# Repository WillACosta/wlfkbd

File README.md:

## The Wolf Split Keyboard

> 3×6 (+2 outer-pinky) Split Keyboard · 3 Thumb Keys · All 1U · MX Compatible

The **WᛝLF Keyboard**, or **wlfkbd**, is a 40-key keyboard featuring only 2 outer-pinky keys to improve ergonomics, white backlight and RGB status LEDs.

> <br>
> Thanks to [JLCCNC](https://jlccnc.com/about-us) for sponsoring the production of the aluminum case. New customers can receive a total of $70 in coupons, so if you haven't used them yet, please check them out.

### Features

- Wireless BLE XIAO nRF52840.
- Ultra-low-profile build (8mm case and 11mm total).
- Lightweight (only 300 g for both halves).
- MX-Spacing.
- Compatible with Gateron KS33/3.0 Low-Profile switches.
- Long battery life (700mAh each half).
- Minimalist design.
- White backlight.
- RGB Status LEDs.

## Firmware & Keymap

The firmware for The Wolf is powered by [ZMK](https://zmk.dev/) and is maintained in its dedicated repository: **[zmk-config-wlf](https://github.com/WillACosta/zmk-config-wlf)**

This repository links the firmware as a Git submodule under [`firmware/`](https://github.com/WillACosta/zmk-config-wlf). To clone both the hardware designs and firmware together:

```bash
git clone --recurse-submodules https://github.com/WillACosta/wlfkbd.git
```

## Documentation

- [Gallery and Keymap](https://willacosta.github.io/wlfkbd/)
- [Build Guide](./docs/build_guide)
- [Measures and Materials tables](./docs/build_guide/tables.md)
- [Flashing Instructions](https://github.com/WillACosta/zmk-config-wlf/blob/main/README.md#flashing-instructions)

## Layout Overview

| Zone      | Columns                | Rows                  | Keys/half | Notes                                       |
| --------- | ---------------------- | --------------------- | --------- | ------------------------------------------- |
| Matrix    | 6 (outer → inner)      | 3 (bottom, home, top) | 17        | Outer column skips bottom row (2 keys only) |
| Thumb     | 3 (inner, home, outer) | 1                     | 3         | Splayed arc, anchored below index           |
| **Total** |                        |                       | **20**    | **40 keys full board**                      |

### Column Stagger Profile

```
         outer  pinky  ring   middle  index  inner
stagger:   —    +u/2   +u/4   +u/4   −u/4   −u/4
mm:        0    +9.525 +4.763 +4.763 −4.763 −4.763
```

**Thumb Cluster Geometry**

| Key         | Splay | Spread          | Stagger | Effective rotation |
| ----------- | ----- | --------------- | ------- | ------------------ |
| thumb_inner | 0°    | u (19.05mm)     | 0mm     | 0°                 |
| thumb_home  | −15°  | u+2.5 (21.55mm) | −2.7mm  | −15°               |
| thumb_outer | −14°  | u+2.5 (21.55mm) | −2.5mm  | −29°               |

The thumb cluster anchors at `matrix_index_bottom` with a `[-0.1u, -1.30u]` offset, placing it slightly left and well below the index column — a natural resting position for the thumb.

> See the Ergogen [config file here](./keyboard/ergogen/config.yml) (used only for the layout diagram)

## Motivations

After stepping into the rabbit hole of "Custom Split Keyboards", I found myself fascinated by this new world of different keyboard layouts, techniques, and a lot of fun!

I have used and own some beloved models created by incredible people, including:

- [Corne](https://github.com/foostan/crkbd)
- [Klor](https://github.com/GEIGEIGEIST/KLOR)
- [Delta/Omega](https://github.com/unspecworks/delta-omega)
- [Lily58](https://github.com/kata0510/Lily58)

The Corne is my favorite keyboard out there (you may notice some similarities between the wlfkbd and crkbd).

Still, I was missing something—that little thing that would improve my experience with the keyboard. Then I started testing different layouts on paper and came up with the layout shown earlier. I even used [Ergo Pad](https://pashutk.com/ergopad/) to find the most comfortable way of typing for my long fingers.

### Features

I'm very fond of good, minimal design, so I've taken inspiration from Apple products, especially the [Magic Keyboard](https://www.ifixit.com/Teardown/Magic+Keyboard+Teardown/50995) and [Magic Trackpad](https://www.ifixit.com/Teardown/Magic+Trackpad+2+Teardown/51032).

I really enjoy the white backlight of the built-in Mac keyboard, so I wanted to implement this in the first revision. Even though I only use the backlight occasionally, it's a nice-to-have for me.

The major feature I present here is the status LED on top of the outer-pinky column. It's something that I really wanted to have in previous keyboards but hadn't.

> For more pictures head to the [gallery](https://willacosta.github.io/wlfkbd/)

## Why "The WᛝLF"?

I really enjoy the symbolism of Wolves, it reminds me of the raw aspect of being human and a strong connection with nature and solitude. Regarding the Norse rune, the "Inguz", it represents "transitions", "new beginnings", "a force of will", etc. I have it tattooed on my right arm, so it's also a personal reference.

## PCB Design

The PCB was built to be ordered already assembled. This means that all components are SMD, so while you may be able to solder them by hand, it requires solid soldering experience.

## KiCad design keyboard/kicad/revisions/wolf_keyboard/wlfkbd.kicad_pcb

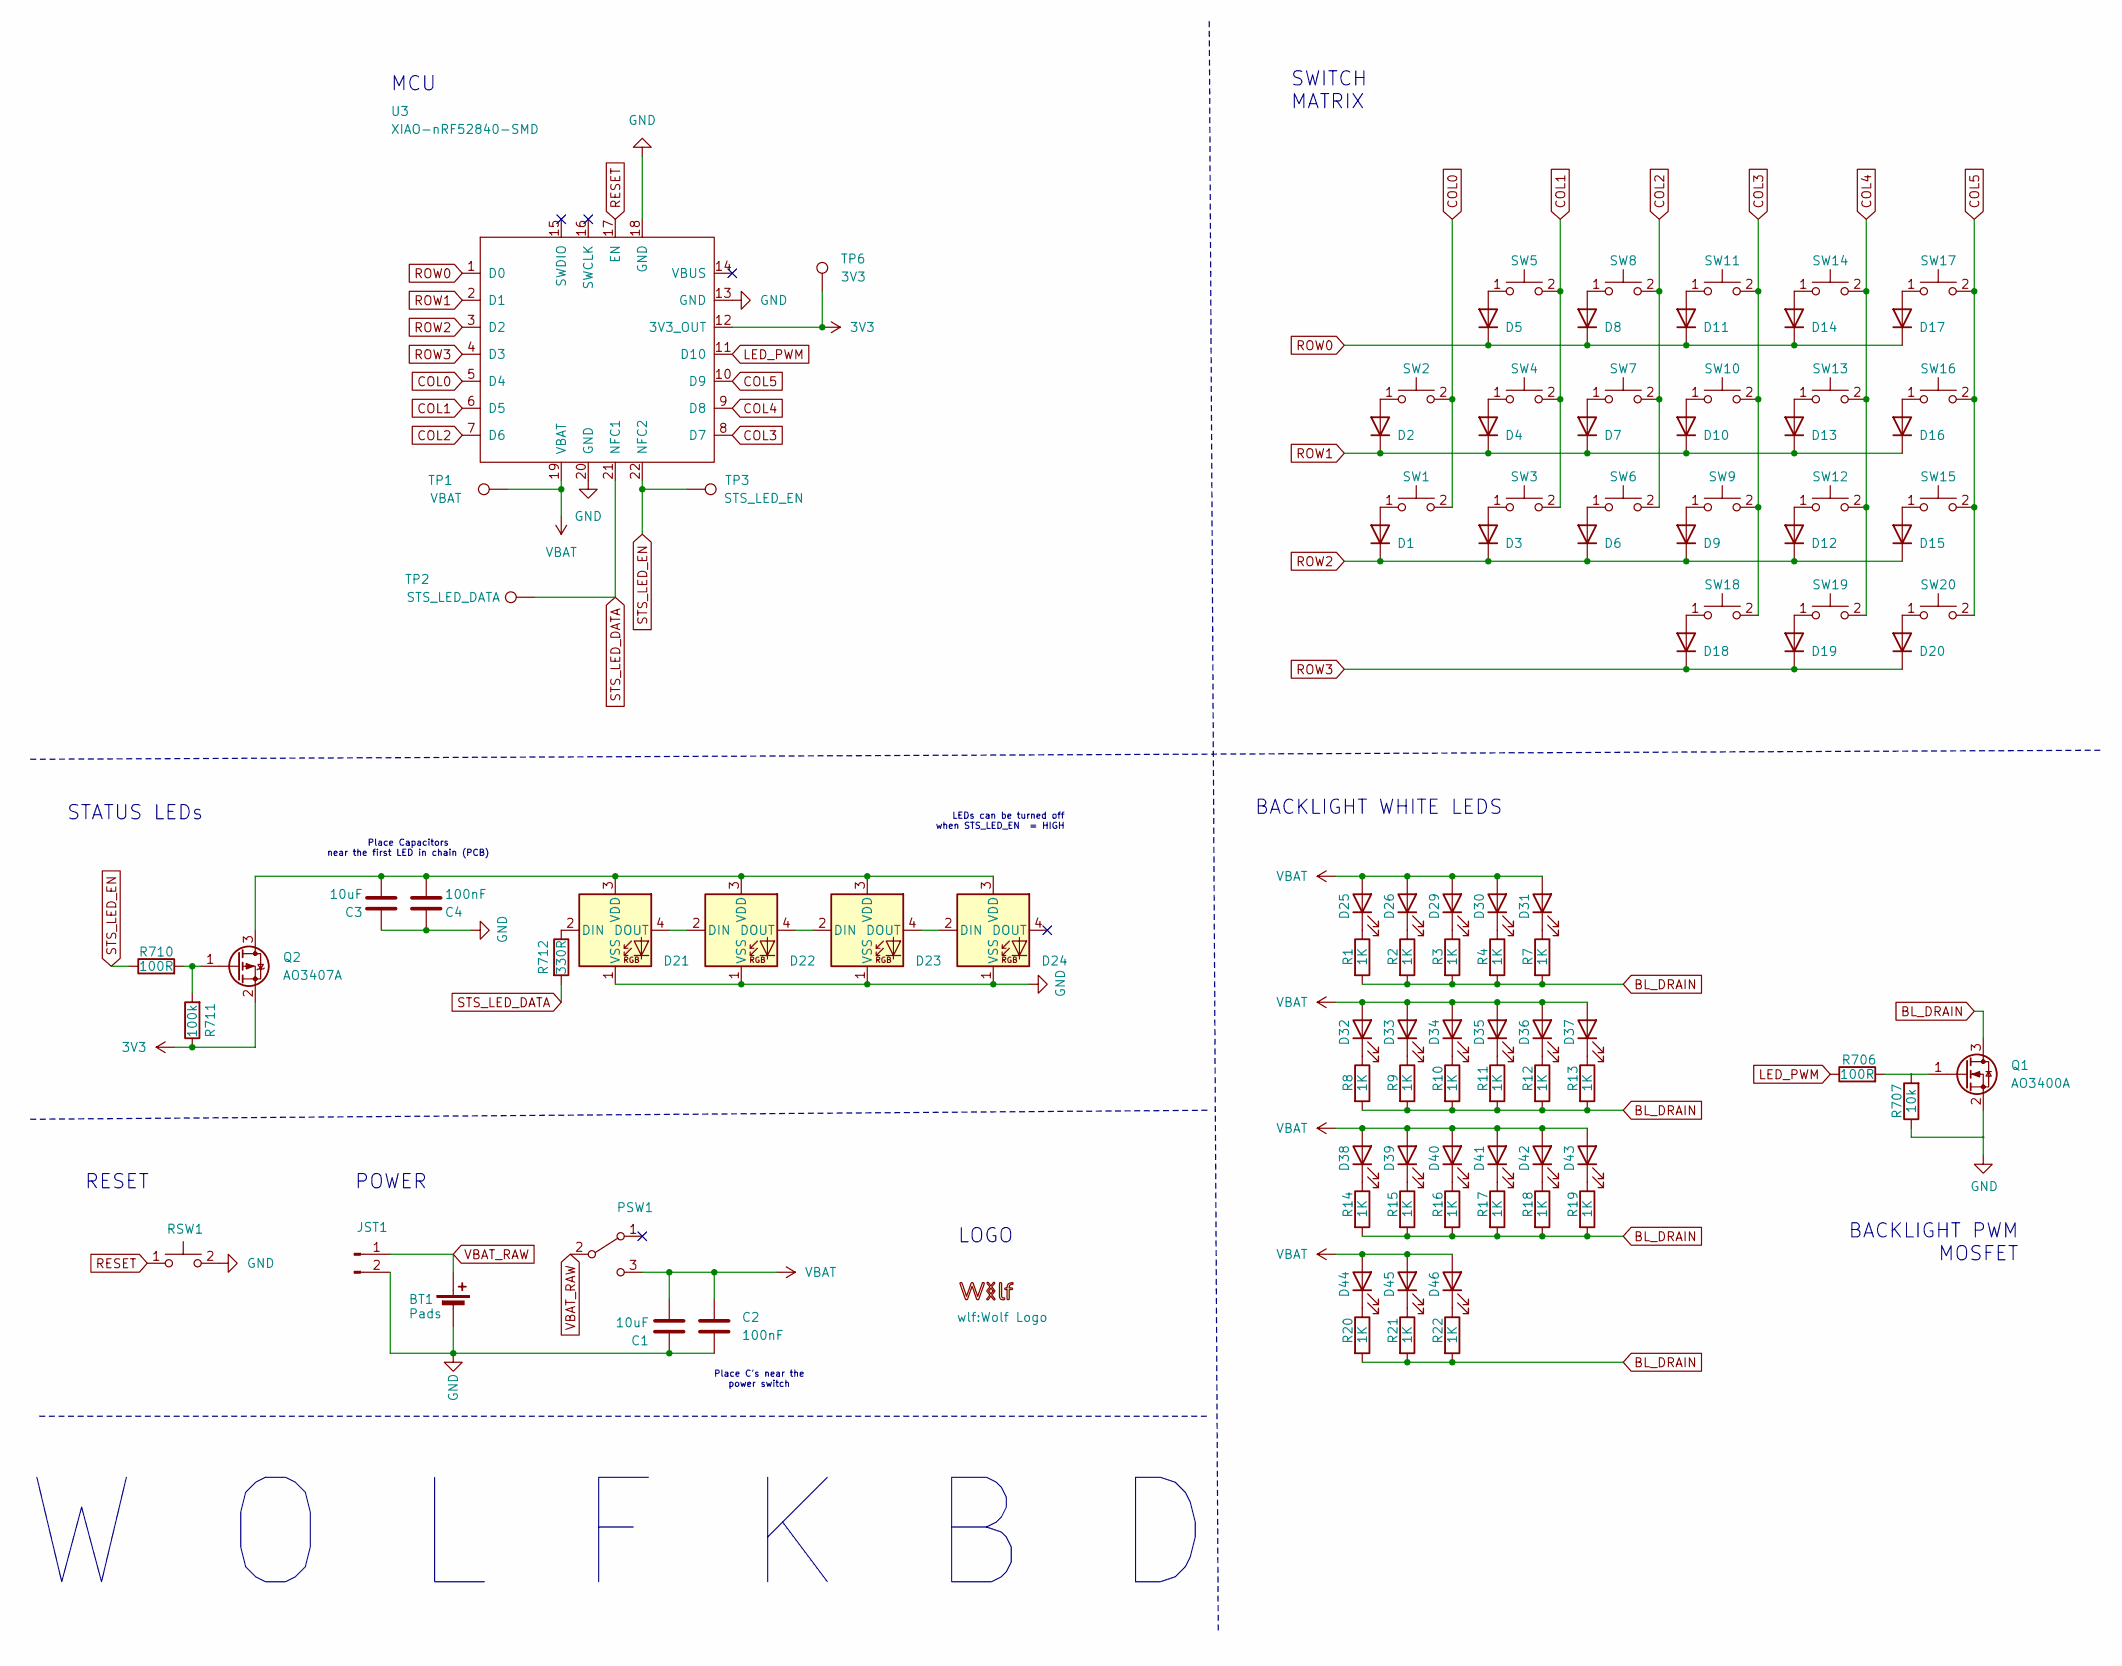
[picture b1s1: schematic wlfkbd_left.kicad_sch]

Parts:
BT1: Pads; Battery_Pad
C1, C3: 10uF; C_0603_1608Metric
C2, C4: 100nF; C_0603_1608Metric
D1, D2, D3, D4, D5, D6, D7, D8, D9, D10, D11, D12, D13, D14, D15, D16, D17, D18, D19, D20: 1N4148W; D_SOD-123
D21, D22, D23, D24: SK6812MINI-E; LED_SK6812MINI-E_3.2x2.8mm_P1.5mm_ReverseMount
D25, D26, D29, D30, D31, D32, D33, D34, D35, D36, D37, D38, D39, D40, D41, D42, D43, D44, D45, D46: LED; LED_MHT151WDT
JST1: Conn_01x02_Pin; JST_GH_SM02B-GHS-TB_1x02-1MP_P1.25mm_Horizontal
LOGO1: Wolf Logo
PSW1: SW_SPDT; SW_MSK12C02-HB
Q1: AO3400A; SOT-23
Q2: AO3407A; SOT-23; MPN AO3407A
R1, R2, R3, R4, R7, R8, R9, R10, R11, R12, R13, R14, R15, R16, R17, R18, R19, R20, R21, R22: 1K; R_0603_1608Metric
R706, R710: 100R; R_0603_1608Metric
R707: 10k; R_0603_1608Metric
R711: 100k; R_0603_1608Metric
R712: 330R; R_0603_1608Metric
RSW1: RSW1; SW_SPST_SKQG_WithStem
SW1, SW2, SW3, SW4, SW5, SW6, SW7, SW8, SW9, SW10, SW11, SW12, SW13, SW14, SW15, SW16, SW17, SW18, SW19, SW20: SW_Push; KS-33B Hotswap 1u
TP1: VBAT; TestPoint_Pad_D1.0mm
TP2: STS_LED_DATA; TestPoint_Pad_D1.0mm
TP3: STS_LED_EN; TestPoint_Pad_D1.0mm
TP6: 3V3; TestPoint_Pad_D1.0mm
U3: XIAO-nRF52840-SMD

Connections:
3V3: Q2.2 (S), R711.1, TP6.1 (1_1), U3.12 (3V3_OUT)
BL_DRAIN: Q1.3 (D), R1.2, R2.2, R3.2, R4.2, R7.2, R8.2, R9.2, R10.2, R11.2, R12.2, R13.2, R14.2, R15.2, R16.2, R17.2, R18.2, R19.2, R20.2, R21.2, R22.2
COL0: SW1.2, SW2.2, U3.5 (D4)
COL1: SW3.2, SW4.2, SW5.2, U3.6 (D5)
COL2: SW6.2, SW7.2, SW8.2, U3.7 (D6)
COL3: SW9.2, SW10.2, SW11.2, SW18.2, U3.8 (D7)
COL4: SW12.2, SW13.2, SW14.2, SW19.2, U3.9 (D8)
COL5: SW15.2, SW16.2, SW17.2, SW20.2, U3.10 (D9)
GND: BT1.2 (-), C1.2, C2.2, C3.1, C4.2, D21.1 (VSS), D22.1 (VSS), D23.1 (VSS), D24.1 (VSS), JST1.2, Q1.2 (S), R707.1, RSW1.2, U3.13 (GND), U3.18 (GND), U3.20 (GND)
LED_PWM: R706.1, U3.11 (D10)
unnamed: D1.2 (A), SW1.1
unnamed: D2.2 (A), SW2.1
unnamed: D3.2 (A), SW3.1
unnamed: D4.2 (A), SW4.1
unnamed: D5.2 (A), SW5.1
unnamed: D6.2 (A), SW6.1
unnamed: D7.2 (A), SW7.1
unnamed: D8.2 (A), SW8.1
unnamed: D9.2 (A), SW9.1
unnamed: D10.2 (A), SW10.1
unnamed: D11.2 (A), SW11.1
unnamed: D12.2 (A), SW12.1
unnamed: D13.2 (A), SW13.1
unnamed: D14.2 (A), SW14.1
unnamed: D15.2 (A), SW15.1
unnamed: D16.2 (A), SW16.1
unnamed: D17.2 (A), SW17.1
unnamed: D18.2 (A), SW18.1
unnamed: D19.2 (A), SW19.1
unnamed: D20.2 (A), SW20.1
unnamed: D21.2 (DIN), R712.1
unnamed: D21.4 (DOUT), D22.2 (DIN)
unnamed: C3.2, C4.1, D21.3 (VDD), D22.3 (VDD), D23.3 (VDD), D24.3 (VDD), Q2.3 (D)
unnamed: D22.4 (DOUT), D23.2 (DIN)
unnamed: D23.4 (DOUT), D24.2 (DIN)
unnamed: D25.1 (K), R1.1
unnamed: D26.1 (K), R2.1
unnamed: D29.1 (K), R3.1
unnamed: D30.1 (K), R4.1
unnamed: D31.1 (K), R7.1
unnamed: D32.1 (K), R8.1
unnamed: D33.1 (K), R9.1
unnamed: D34.1 (K), R10.1
unnamed: D35.1 (K), R11.1
unnamed: D36.1 (K), R12.1
unnamed: D37.1 (K), R13.1
unnamed: D38.1 (K), R14.1
unnamed: D39.1 (K), R15.1
unnamed: D40.1 (K), R16.1
unnamed: D41.1 (K), R17.1
unnamed: D42.1 (K), R18.1
unnamed: D43.1 (K), R19.1
unnamed: D44.1 (K), R20.1
unnamed: D45.1 (K), R21.1
unnamed: D46.1 (K), R22.1
unnamed: Q1.1 (G), R706.2, R707.2
unnamed: Q2.1 (G), R710.2, R711.2
RESET: RSW1.1, U3.17 (EN)
ROW0: D5.1 (K), D8.1 (K), D11.1 (K), D14.1 (K), D17.1 (K), U3.1 (D0)
ROW1: D2.1 (K), D4.1 (K), D7.1 (K), D10.1 (K), D13.1 (K), D16.1 (K), U3.2 (D1)
ROW2: D1.1 (K), D3.1 (K), D6.1 (K), D9.1 (K), D12.1 (K), D15.1 (K), U3.3 (D2)
ROW3: D18.1 (K), D19.1 (K), D20.1 (K), U3.4 (D3)
STS_LED_DATA: R712.2, TP2.1 (1_1), U3.21 (NFC1)
STS_LED_EN: R710.1, TP3.1 (1_1), U3.22 (NFC2)
VBAT: C1.1, C2.1, D25.2 (A), D26.2 (A), D29.2 (A), D30.2 (A), D31.2 (A), D32.2 (A), D33.2 (A), D34.2 (A), D35.2 (A), D36.2 (A), D37.2 (A), D38.2 (A), D39.2 (A), D40.2 (A), D41.2 (A), D42.2 (A), D43.2 (A), D44.2 (A), D45.2 (A), D46.2 (A), PSW1.3 (C), TP1.1 (1_1), U3.19 (VBAT)
VBAT_RAW: BT1.1 (+), JST1.1, PSW1.2 (B)

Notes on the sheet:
W O L F K B D
LOGO
MCU
LEDs can be turned off when STS_LED_EN = HIGH
RESET
Place C's near the power switch
Place Capacitors near the first LED in chain (PCB)
BACKLIGHT PWM MOSFET
POWER
STATUS LEDs
BACKLIGHT WHITE LEDS
SWITCH MATRIX

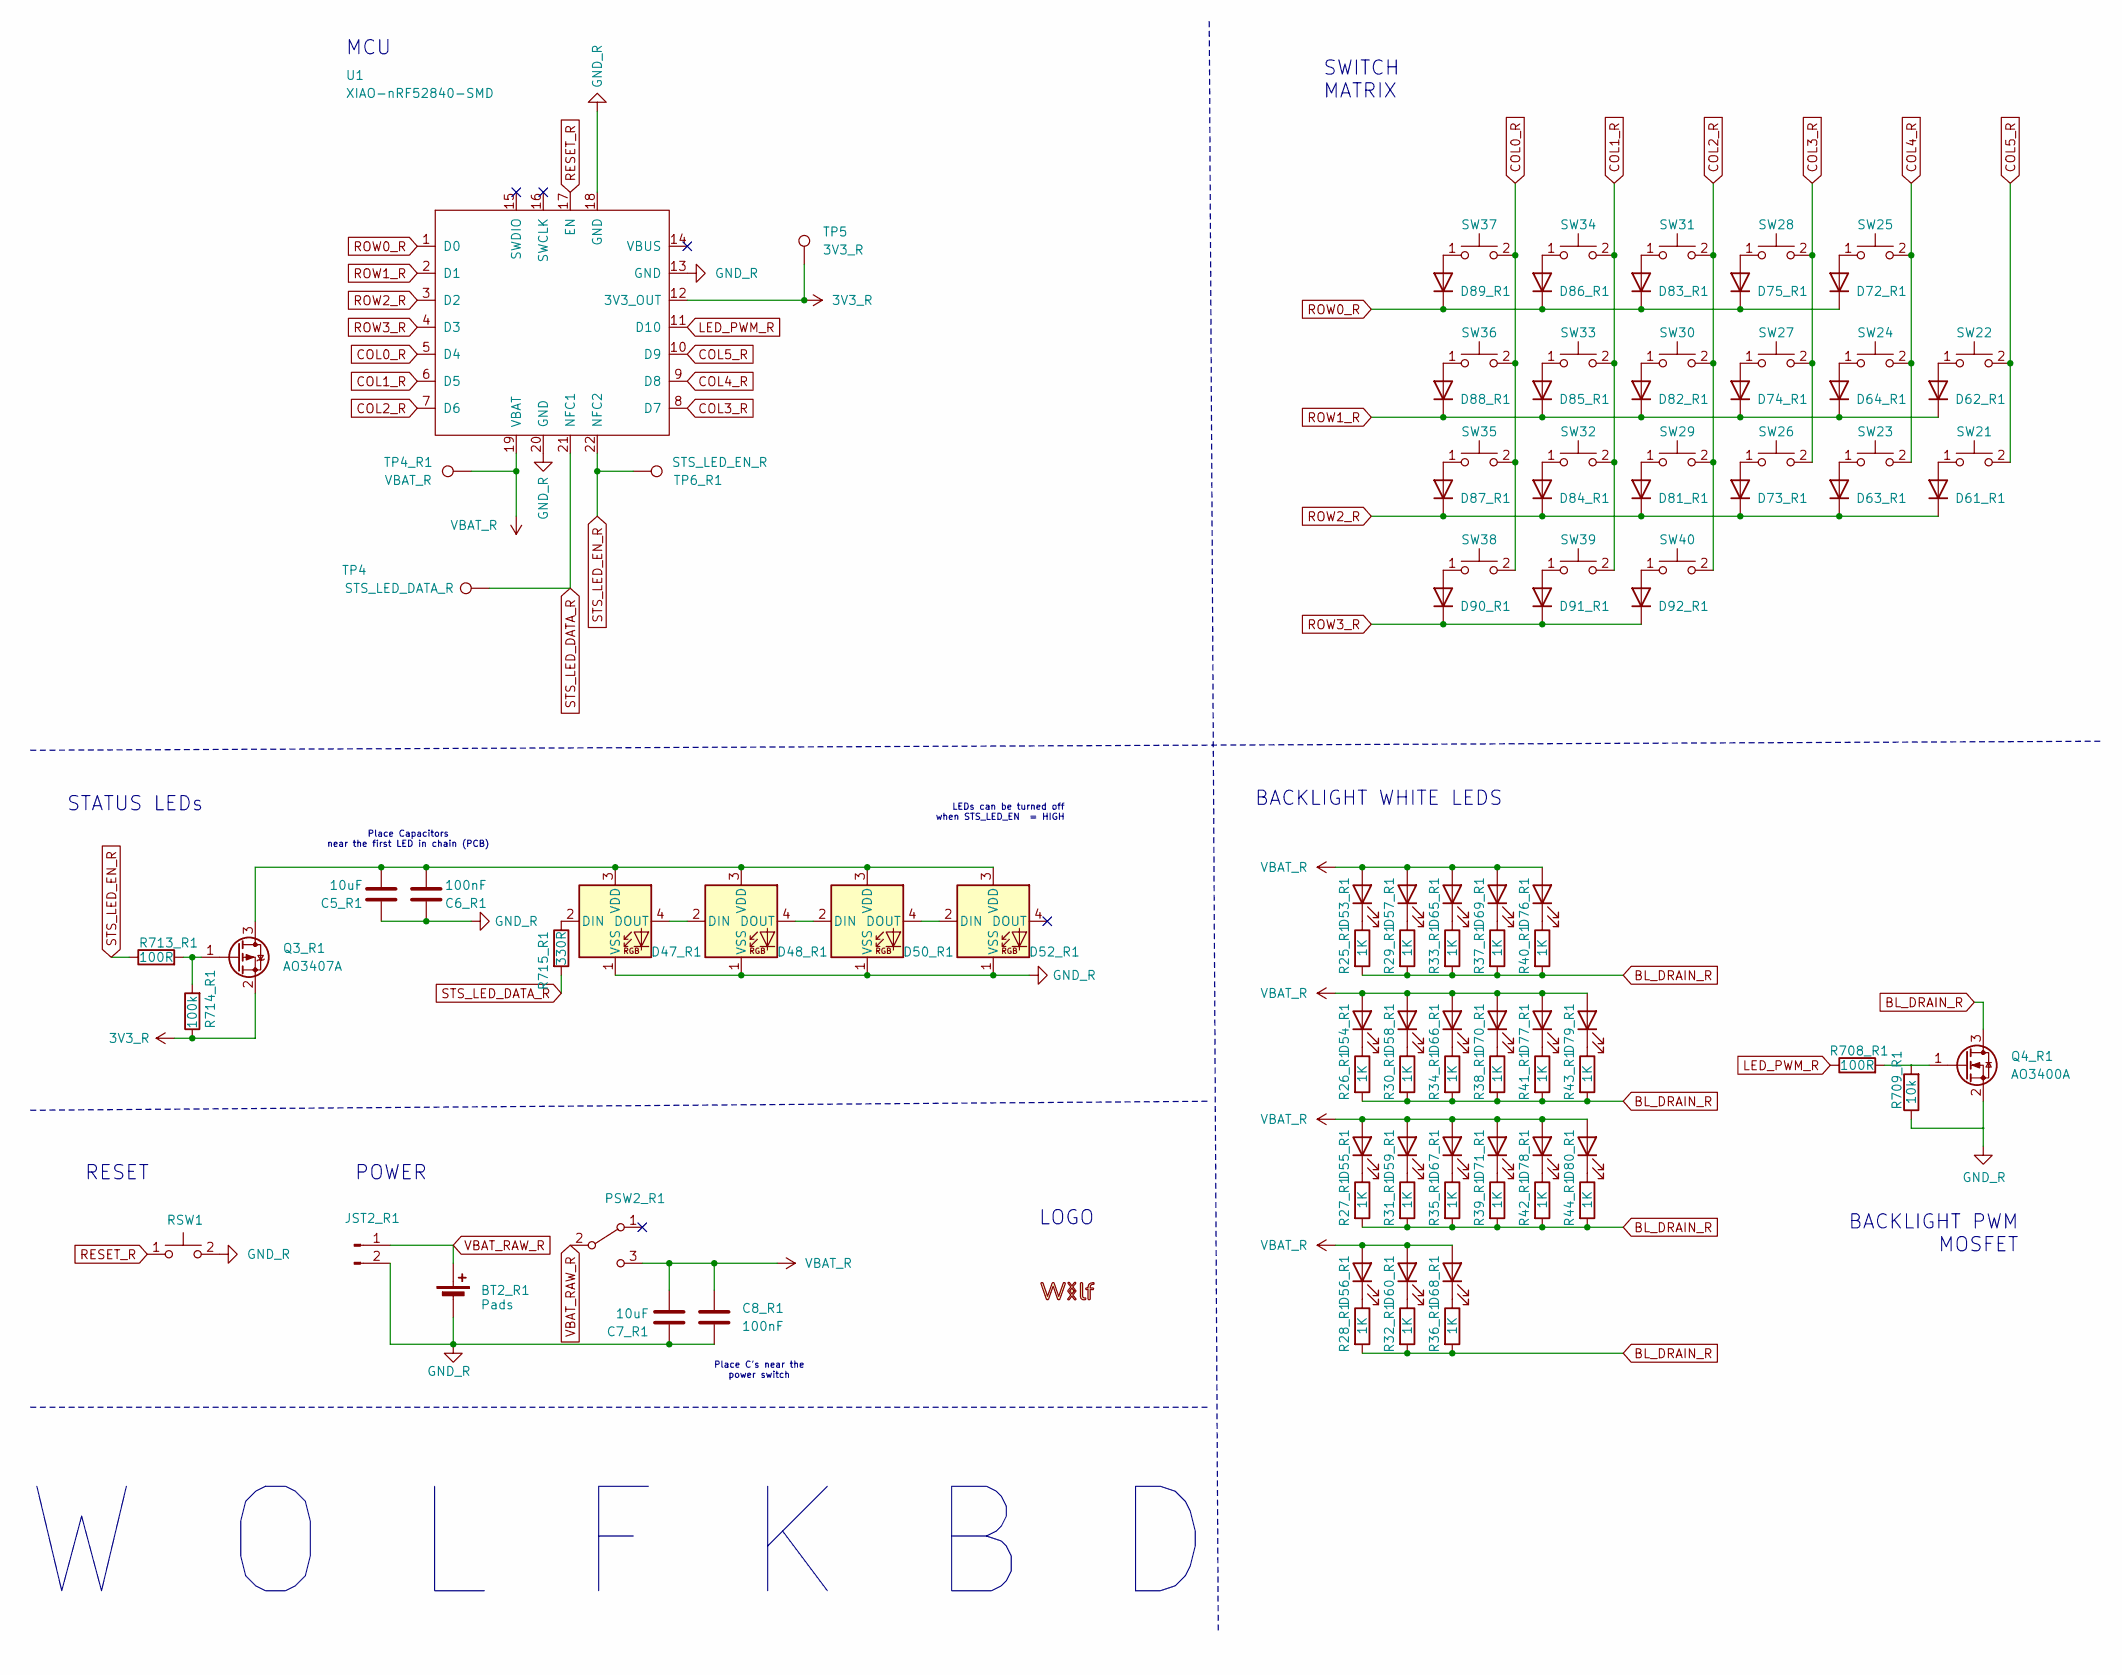
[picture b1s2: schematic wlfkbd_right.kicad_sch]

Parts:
3V3_R03, 3V3_R04: 3V3_R
BT2_R1: Pads; Battery_Pad
C5_R1, C7_R1: 10uF; C_0603_1608Metric
C6_R1, C8_R1: 100nF; C_0603_1608Metric
D47_R1, D48_R1, D50_R1, D52_R1: SK6812MINI-E; LED_SK6812MINI-E_3.2x2.8mm_P1.5mm_ReverseMount
D53_R1, D54_R1, D55_R1, D56_R1, D57_R1, D58_R1, D59_R1, D60_R1, D65_R1, D66_R1, D67_R1, D68_R1, D69_R1, D70_R1, D71_R1, D76_R1, D77_R1, D78_R1, D79_R1, D80_R1: LED; LED_MHT151WDT
D61_R1, D62_R1, D63_R1, D64_R1, D72_R1, D73_R1, D74_R1, D75_R1, D81_R1, D82_R1, D83_R1, D84_R1, D85_R1, D86_R1, D87_R1, D88_R1, D89_R1, D90_R1, D91_R1, D92_R1: 1N4148W; D_SOD-123
GND_R05, GND_R06, GND_R07, GND_R08, GND_R09: GND_R
JST2_R1: Conn_01x02_Pin; JST_GH_SM02B-GHS-TB_1x02-1MP_P1.25mm_Horizontal
LOGO_R1: Wolf Logo
PSW2_R1: SW_SPDT; SW_MSK12C02-HB
Q3_R1: AO3407A; SOT-23; MPN AO3407A
Q4_R1: AO3400A; SOT-23
R25_R1, R26_R1, R27_R1, R28_R1, R29_R1, R30_R1, R31_R1, R32_R1, R33_R1, R34_R1, R35_R1, R36_R1, R37_R1, R38_R1, R39_R1, R40_R1, R41_R1, R42_R1, R43_R1, R44_R1: 1K; R_0603_1608Metric
R708_R1, R713_R1: 100R; R_0603_1608Metric
R709_R1: 10k; R_0603_1608Metric
R714_R1: 100k; R_0603_1608Metric
R715_R1: 330R; R_0603_1608Metric
RSW2_R1: RSW1; SW_SPST_SKQG_WithStem
SW21, SW22, SW23, SW24, SW25, SW26, SW27, SW28, SW29, SW30, SW31, SW32, SW33, SW34, SW35, SW36, SW37, SW38, SW39, SW40: SW_Push; KS-33B Hotswap 1u
TP4: STS_LED_DATA_R; TestPoint_Pad_D1.0mm
TP4_R1: VBAT_R; TestPoint_Pad_D1.0mm
TP5: 3V3_R; TestPoint_Pad_D1.0mm
TP6_R1: STS_LED_EN_R; TestPoint_Pad_D1.0mm
U1: XIAO-nRF52840-SMD
VBAT_R01: VBAT_R

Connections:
BL_DRAIN_R: Q4_R1.3 (D), R25_R1.2, R26_R1.2, R27_R1.2, R28_R1.2, R29_R1.2, R30_R1.2, R31_R1.2, R32_R1.2, R33_R1.2, R34_R1.2, R35_R1.2, R36_R1.2, R37_R1.2, R38_R1.2, R39_R1.2, R40_R1.2, R41_R1.2, R42_R1.2, R43_R1.2, R44_R1.2
COL0_R: SW35.2, SW36.2, SW37.2, SW38.2, U1.5 (D4)
COL1_R: SW32.2, SW33.2, SW34.2, SW39.2, U1.6 (D5)
COL2_R: SW29.2, SW30.2, SW31.2, SW40.2, U1.7 (D6)
COL3_R: SW26.2, SW27.2, SW28.2, U1.8 (D7)
COL4_R: SW23.2, SW24.2, SW25.2, U1.9 (D8)
COL5_R: SW21.2, SW22.2, U1.10 (D9)
LED_PWM_R: R708_R1.1, U1.11 (D10)
unnamed: D47_R1.2 (DIN), R715_R1.1
unnamed: D47_R1.4 (DOUT), D48_R1.2 (DIN)
unnamed: C5_R1.2, C6_R1.1, D47_R1.3 (VDD), D48_R1.3 (VDD), D50_R1.3 (VDD), D52_R1.3 (VDD), Q3_R1.3 (D)
unnamed: D48_R1.4 (DOUT), D50_R1.2 (DIN)
unnamed: D50_R1.4 (DOUT), D52_R1.2 (DIN)
unnamed: D53_R1.1 (K), R25_R1.1
unnamed: D54_R1.1 (K), R26_R1.1
unnamed: D55_R1.1 (K), R27_R1.1
unnamed: D56_R1.1 (K), R28_R1.1
unnamed: D57_R1.1 (K), R29_R1.1
unnamed: D58_R1.1 (K), R30_R1.1
unnamed: D59_R1.1 (K), R31_R1.1
unnamed: D60_R1.1 (K), R32_R1.1
unnamed: D61_R1.2 (A), SW21.1
unnamed: D62_R1.2 (A), SW22.1
unnamed: D63_R1.2 (A), SW23.1
unnamed: D64_R1.2 (A), SW24.1
unnamed: D65_R1.1 (K), R33_R1.1
unnamed: D66_R1.1 (K), R34_R1.1
unnamed: D67_R1.1 (K), R35_R1.1
unnamed: D68_R1.1 (K), R36_R1.1
unnamed: D69_R1.1 (K), R37_R1.1
unnamed: D70_R1.1 (K), R38_R1.1
unnamed: D71_R1.1 (K), R39_R1.1
unnamed: D72_R1.2 (A), SW25.1
unnamed: D73_R1.2 (A), SW26.1
unnamed: D74_R1.2 (A), SW27.1
unnamed: D75_R1.2 (A), SW28.1
unnamed: D76_R1.1 (K), R40_R1.1
unnamed: D77_R1.1 (K), R41_R1.1
unnamed: D78_R1.1 (K), R42_R1.1
unnamed: D79_R1.1 (K), R43_R1.1
unnamed: D80_R1.1 (K), R44_R1.1
unnamed: D81_R1.2 (A), SW29.1
unnamed: D82_R1.2 (A), SW30.1
unnamed: D83_R1.2 (A), SW31.1
unnamed: D84_R1.2 (A), SW32.1
unnamed: D85_R1.2 (A), SW33.1
unnamed: D86_R1.2 (A), SW34.1
unnamed: D87_R1.2 (A), SW35.1
unnamed: D88_R1.2 (A), SW36.1
unnamed: D89_R1.2 (A), SW37.1
unnamed: D90_R1.2 (A), SW38.1
unnamed: D91_R1.2 (A), SW39.1
unnamed: D92_R1.2 (A), SW40.1
unnamed: Q3_R1.1 (G), R713_R1.2, R714_R1.2
unnamed: Q4_R1.1 (G), R708_R1.2, R709_R1.2
RESET_R: RSW2_R1.1, U1.17 (EN)
ROW0_R: D72_R1.1 (K), D75_R1.1 (K), D83_R1.1 (K), D86_R1.1 (K), D89_R1.1 (K), U1.1 (D0)
ROW1_R: D62_R1.1 (K), D64_R1.1 (K), D74_R1.1 (K), D82_R1.1 (K), D85_R1.1 (K), D88_R1.1 (K), U1.2 (D1)
ROW2_R: D61_R1.1 (K), D63_R1.1 (K), D73_R1.1 (K), D81_R1.1 (K), D84_R1.1 (K), D87_R1.1 (K), U1.3 (D2)
ROW3_R: D90_R1.1 (K), D91_R1.1 (K), D92_R1.1 (K), U1.4 (D3)
STS_LED_DATA_R: R715_R1.2, TP4.1 (1_1), U1.21 (NFC1)
STS_LED_EN_R: R713_R1.1, TP6_R1.1 (1_1), U1.22 (NFC2)
VBAT_RAW_R: BT2_R1.1 (+), JST2_R1.1, PSW2_R1.2 (B)

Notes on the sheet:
STATUS LEDs
SWITCH MATRIX
Place C's near the power switch
W O L F K B D
MCU
RESET
BACKLIGHT PWM MOSFET
LEDs can be turned off when STS_LED_EN = HIGH
LOGO
Place Capacitors near the first LED in chain (PCB)
BACKLIGHT WHITE LEDS
POWER

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
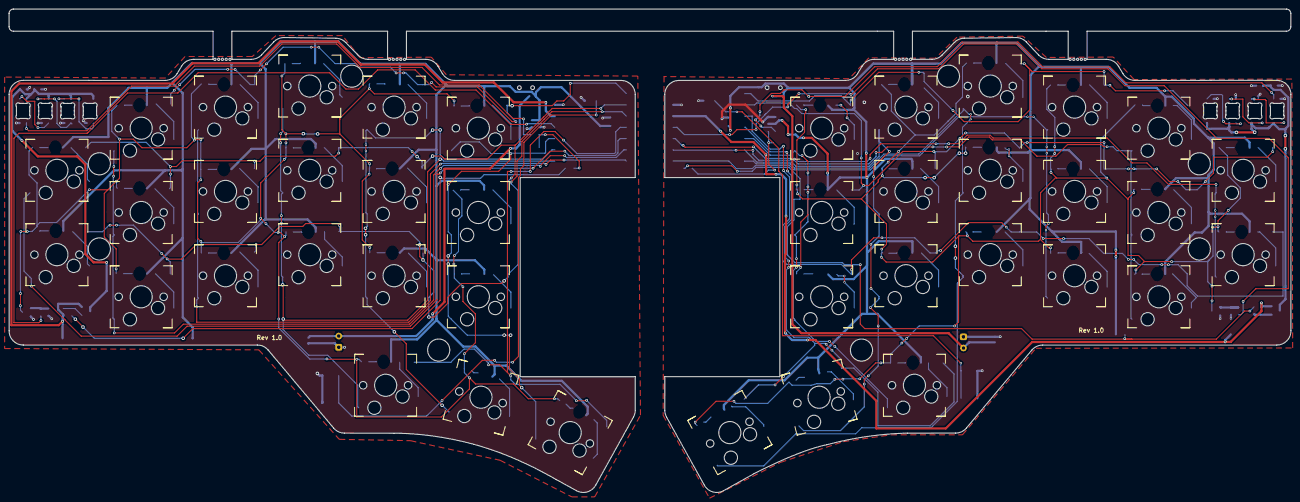
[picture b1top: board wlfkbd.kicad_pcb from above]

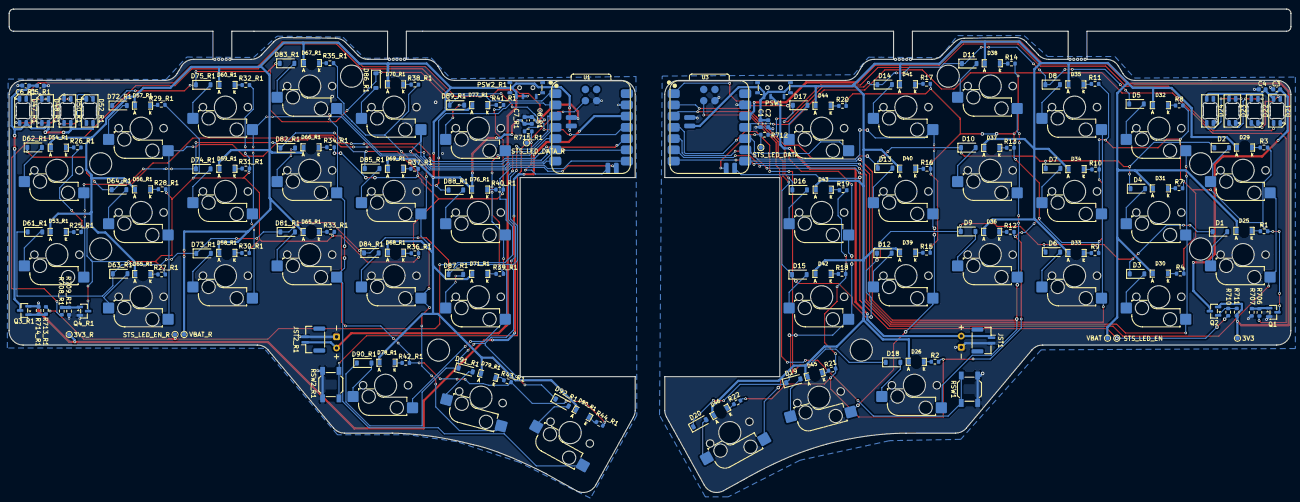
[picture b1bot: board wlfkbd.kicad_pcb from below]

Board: 2 copper layers, 289.7 x 109.2 mm, 210 parts (208 on the bottom side), 132 nets.
